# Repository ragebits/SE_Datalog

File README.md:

# SE_Datalog
Diseño de la placa para SE

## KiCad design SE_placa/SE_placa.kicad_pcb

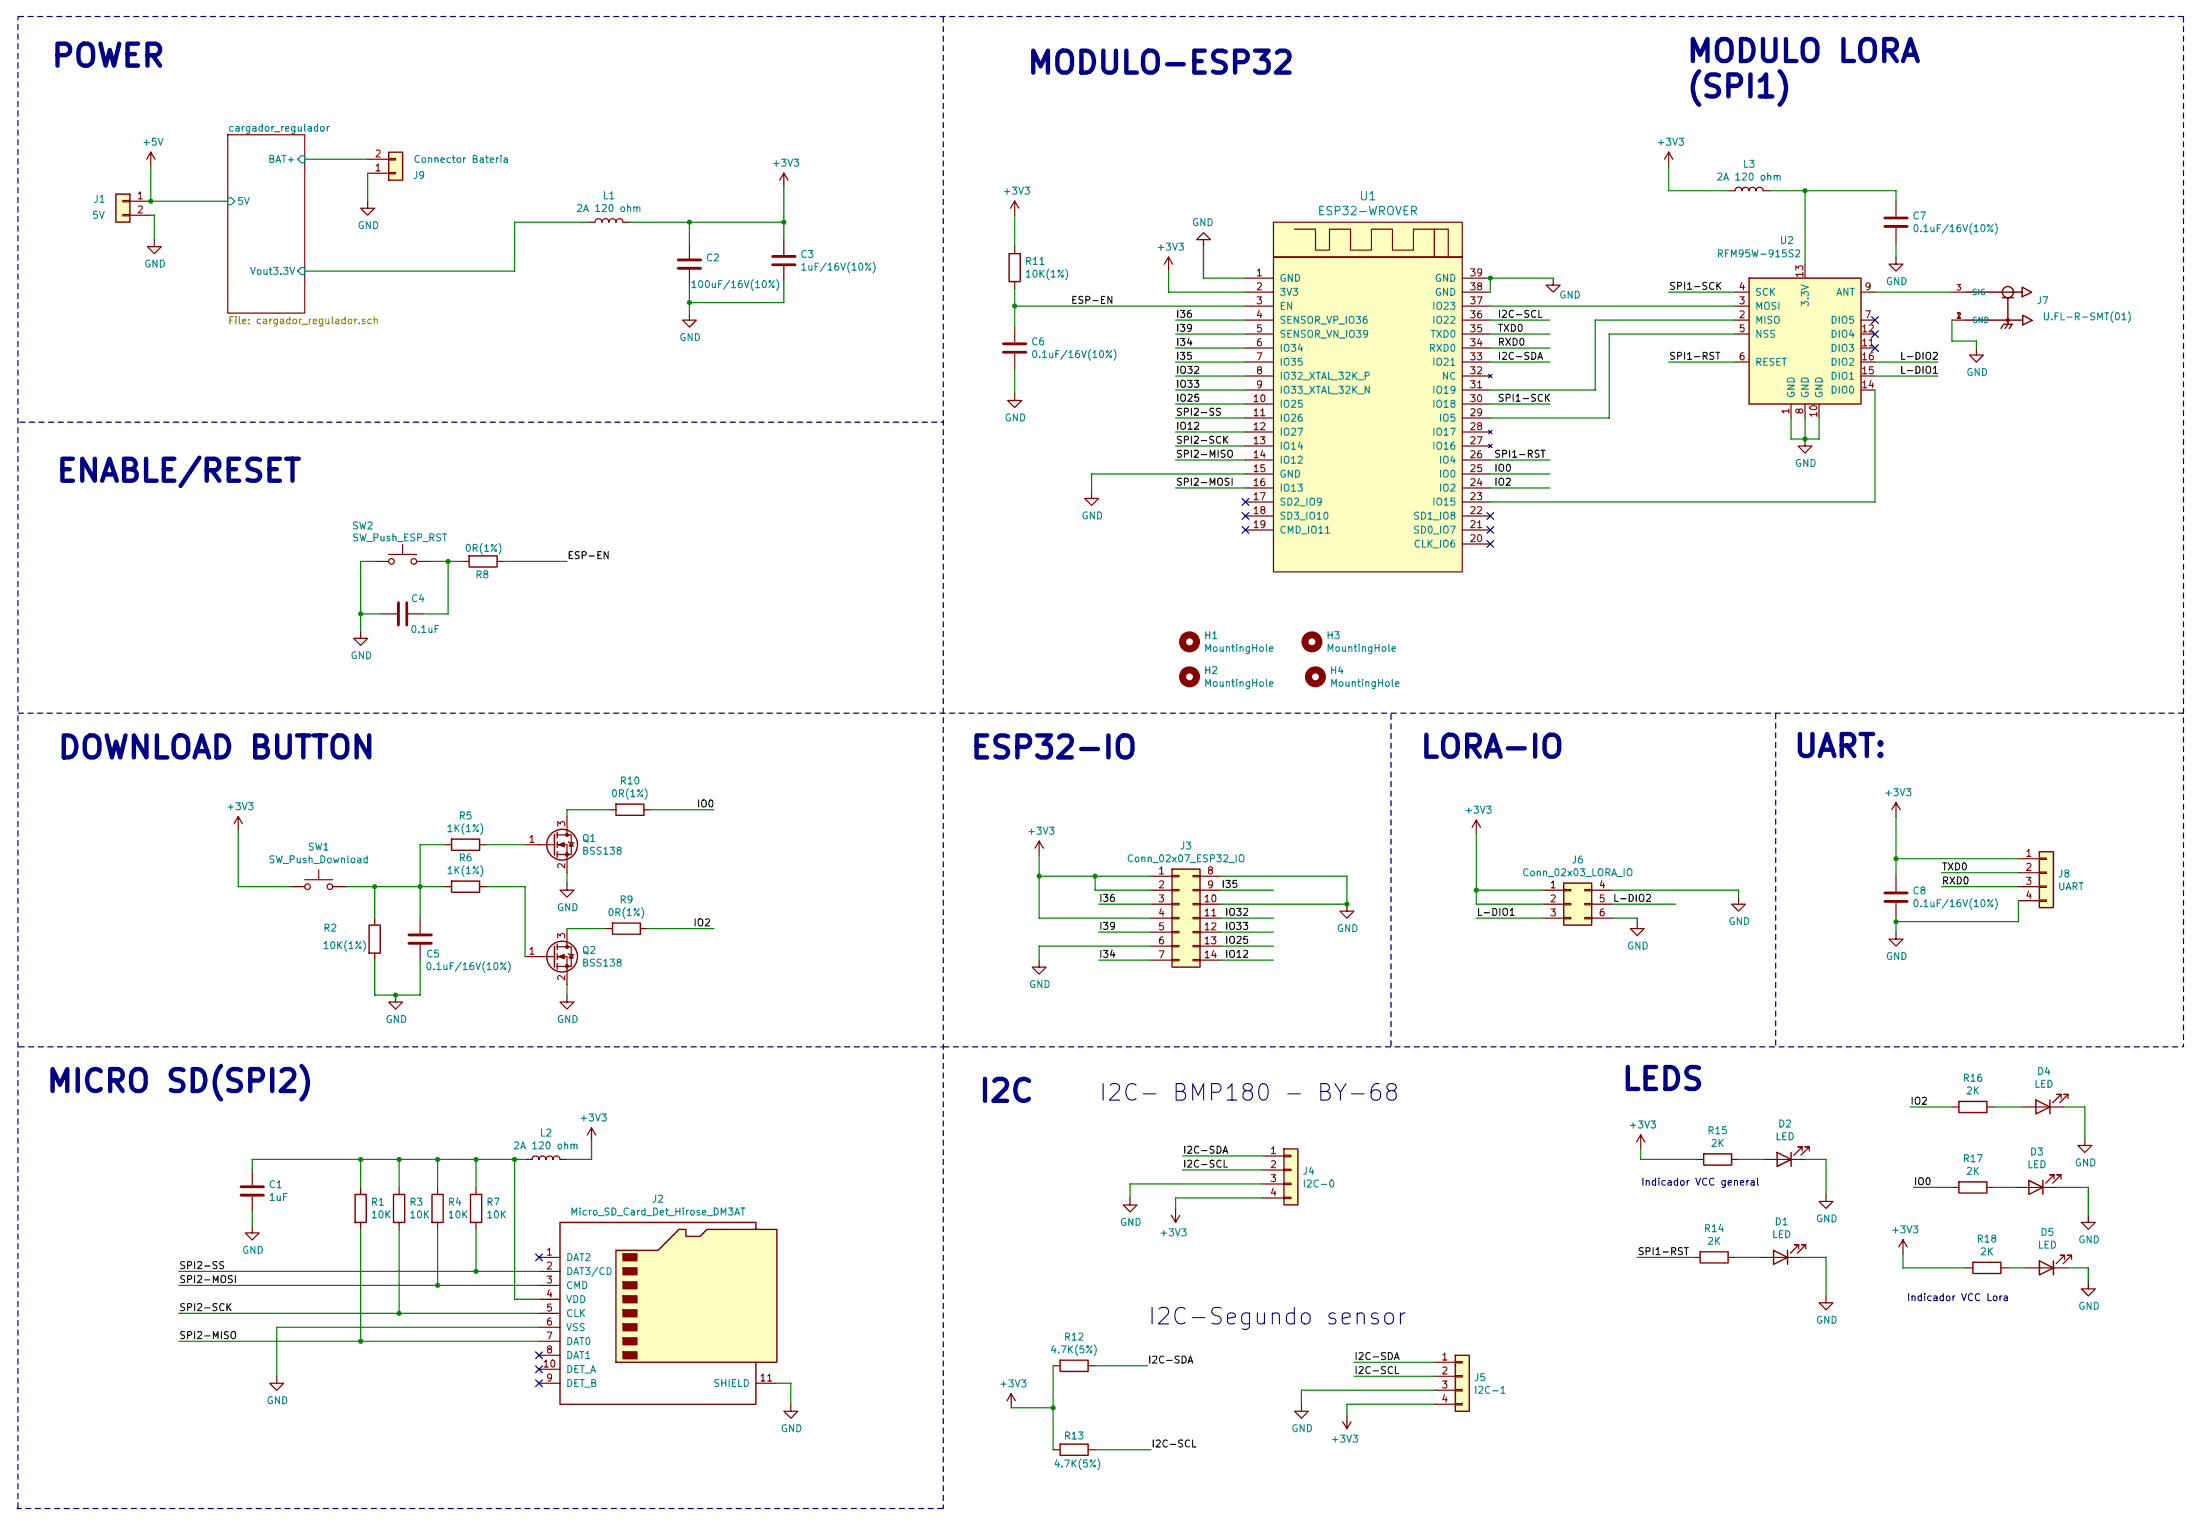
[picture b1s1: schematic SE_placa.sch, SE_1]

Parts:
C1: 1uF; C_0805_2012Metric_Pad1.18x1.45mm_HandSolder
C2: 100uF/16V(10%); C_0805_2012Metric_Pad1.18x1.45mm_HandSolder
C3: 1uF/16V(10%); C_0805_2012Metric_Pad1.18x1.45mm_HandSolder
C4: 0.1uF; C_0805_2012Metric_Pad1.18x1.45mm_HandSolder
C5, C6, C7, C8: 0.1uF/16V(10%); C_0805_2012Metric_Pad1.18x1.45mm_HandSolder
D1, D2, D3, D4, D5: LED; LED_0805_2012Metric_Pad1.15x1.40mm_HandSolder
H1, H2, H3, H4: MountingHole; MountingHole_2.5mm_Pad
J1: 5V; PinHeader_1x02_P2.54mm_Vertical
J2: Micro_SD_Card_Det_Hirose_DM3AT; microSD_HC_Hirose_DM3AT-SF-PEJM5
J3: Conn_02x07_ESP32_IO; PinSocket_2x07_P2.54mm_Vertical
J4: I2C-0; PinSocket_1x04_P2.54mm_Vertical
J5: I2C-1; PinSocket_1x04_P2.54mm_Vertical
J6: Conn_02x03_LORA_IO; PinSocket_2x03_P2.54mm_Vertical
J7: U.FL-R-SMT(01); HRS_U.FL-R-SMT(01)
J8: UART; PinSocket_1x04_P2.54mm_Vertical
J9: Connector Bateria; PinHeader_1x02_P2.54mm_Vertical
L1, L2, L3: 2A 120 ohm; L_0805_2012Metric_Pad1.15x1.40mm_HandSolder
Q1, Q2: BSS138; SOT-23
R1, R3, R4, R7: 10K; R_0805_2012Metric_Pad1.20x1.40mm_HandSolder
R2, R11: 10K(1%); R_0805_2012Metric_Pad1.20x1.40mm_HandSolder
R5, R6: 1K(1%); R_0805_2012Metric_Pad1.20x1.40mm_HandSolder
R8, R9, R10: 0R(1%); R_0805_2012Metric_Pad1.20x1.40mm_HandSolder
R12, R13: 4.7K(5%); R_0805_2012Metric_Pad1.20x1.40mm_HandSolder
R14, R15, R16, R17, R18: 2K; R_0805_2012Metric_Pad1.20x1.40mm_HandSolder
SW1: SW_Push_Download; SW_SPST_CK_RS282G05A3
SW2: SW_Push_ESP_RST; SW_SPST_CK_RS282G05A3
U1: ESP32-WROVER; XCVR_ESP32-WROVER-I
U2: RFM95W-915S2; HOPERF_RFM9XW_SMD

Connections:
+3V3: C2.1, C3.1, C8.1, J3.1, J3.2, J3.4, J4.4, J5.4, J6.1, J6.2, J8.1, L1.2, L2.2, L3.1, R11.2, R12.2, R13.2, R15.2, R18.2, SW1.1, U1.2 (3V3)
+5V: J1.1; also elsewhere on the board
/ESP-EN: C6.2, R8.1, R11.1, U1.3 (EN)
/I2C-SCL: J4.2, J5.2, R13.1, U1.36 (IO22)
/I2C-SDA: J4.1, J5.1, R12.1, U1.33 (IO21)
/I34: J3.7, U1.6 (IO34)
/I35: J3.9, U1.7 (IO35)
/I36: J3.3, U1.4 (SENSOR_VP_IO36)
/I39: J3.5, U1.5 (SENSOR_VN_IO39)
/IO0: R10.1, R17.2, U1.25 (IO0)
/IO2: R9.1, R16.2, U1.24 (IO2)
/IO12: J3.14, U1.12 (IO27)
/IO25: J3.13, U1.10 (IO25)
/IO32: J3.11, U1.8 (IO32_XTAL_32K_P)
/IO33: J3.12, U1.9 (IO33_XTAL_32K_N)
/L-DIO1: J6.3, U2.15 (DIO1)
/L-DIO2: J6.5, U2.16 (DIO2)
/RXD0: J8.3, U1.34 (RXD0)
/SPI1-RST: R14.2, U1.26 (IO4), U2.6 (RESET)
/SPI1-SCK: U1.30 (IO18), U2.4 (SCK)
/SPI2-MISO: J2.7 (DAT0), R1.2, U1.14 (IO12)
/SPI2-MOSI: J2.3 (CMD), R4.2, U1.16 (IO13)
/SPI2-SCK: J2.5 (CLK), R3.2, U1.13 (IO14)
/SPI2-SS: J2.2 (DAT3/CD), R7.2, U1.11 (IO26)
/TXD0: J8.2, U1.35 (TXD0)
/cargador_regulador/BAT+: J9.2; also elsewhere on the board
/cargador_regulador/Vout3.3V: L1.1; also elsewhere on the board
GND: C1.2, C2.2, C3.2, C4.2, C5.2, C6.1, C7.2, C8.2, D1.1 (K), D2.1 (K), D3.1 (K), D4.1 (K), D5.1 (K), J1.2, J2.6 (VSS), J2.11 (SHIELD), J3.6, J3.8, J3.10, J4.3, J5.3, J6.4, J6.6, J7.1 (GND), J7.2 (GND), J8.4, J9.1, Q1.2 (S), Q2.2 (S), R2.2, SW2.1, U1.1 (GND), U1.15 (GND), U1.38 (GND), U1.39 (GND), U2.1 (GND), U2.8 (GND), U2.10 (GND); also elsewhere on the board
unnamed: C1.1, J2.4 (VDD), L2.1, R1.1, R3.1, R4.1, R7.1
unnamed: C4.1, R8.2, SW2.2
unnamed: C5.1, R2.1, R5.2, R6.2, SW1.2
unnamed: C7.1, L3.2, U2.13 (3.3V)
unnamed: D1.2 (A), R14.1
unnamed: D2.2 (A), R15.1
unnamed: D3.2 (A), R17.1
unnamed: D4.2 (A), R16.1
unnamed: D5.2 (A), R18.1
unnamed: J7.3 (SIG), U2.9 (ANT)
unnamed: Q1.1 (G), R5.1
unnamed: Q1.3 (D), R10.2
unnamed: Q2.1 (G), R6.1
unnamed: Q2.3 (D), R9.2
unnamed: U1.23 (IO15), U2.14 (DIO0)
unnamed: U1.29 (IO5), U2.5 (NSS)
unnamed: U1.31 (IO19), U2.2 (MISO)
unnamed: U1.37 (IO23), U2.3 (MOSI)

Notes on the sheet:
POWER
I2C- BMP180 - BY-68
MICRO SD(SPI2)
MODULO-ESP32
MODULO LORA (SPI1)
DOWNLOAD BUTTON
ENABLE/RESET
LEDS
LORA-IO
I2C
I2C-Segundo sensor
ESP32-IO
UART:
Indicador VCC general
Indicador VCC Lora

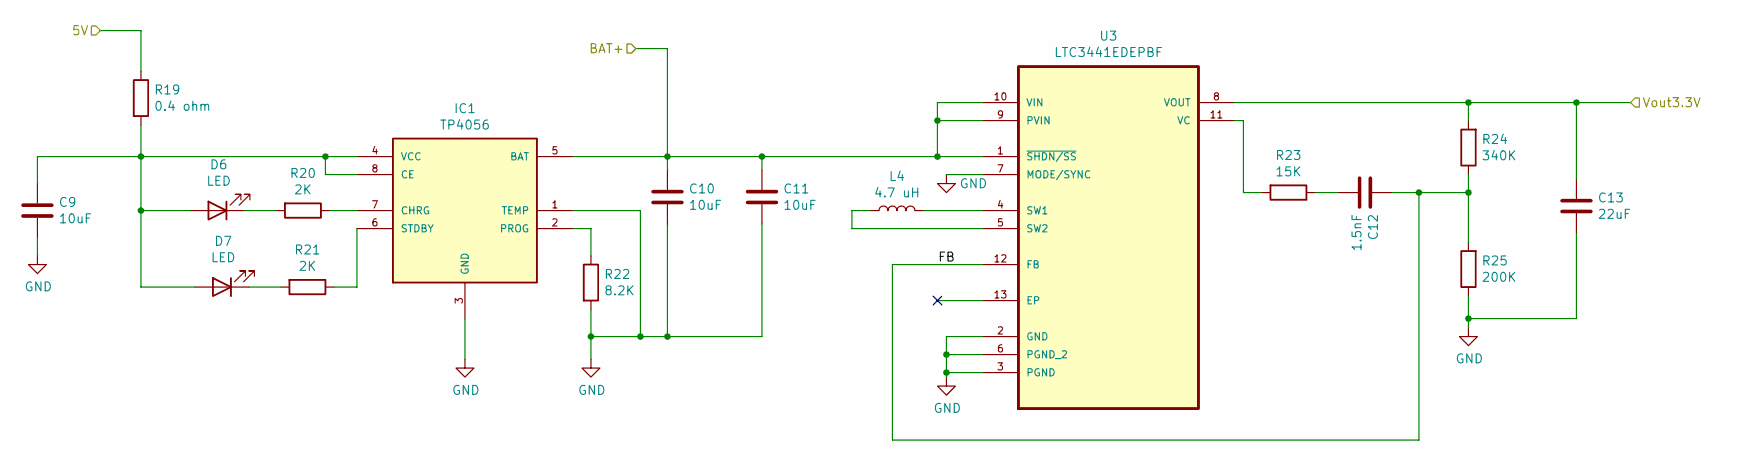
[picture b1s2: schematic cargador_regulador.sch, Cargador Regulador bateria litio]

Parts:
C9, C10, C11: 10uF; C_0805_2012Metric_Pad1.18x1.45mm_HandSolder
C12: 1.5nF; C_0805_2012Metric_Pad1.18x1.45mm_HandSolder
C13: 22uF; C_0805_2012Metric_Pad1.18x1.45mm_HandSolder
D6, D7: LED; LED_0805_2012Metric_Pad1.15x1.40mm_HandSolder
IC1: TP4056; SOP-8
L4: 4.7 uH; IND_1264EY-4R7M=P3
R19: 0.4 ohm; R_0805_2012Metric_Pad1.20x1.40mm_HandSolder
R20, R21: 2K; R_0805_2012Metric_Pad1.20x1.40mm_HandSolder
R22: 8.2K; R_0805_2012Metric_Pad1.20x1.40mm_HandSolder
R23: 15K; R_0805_2012Metric_Pad1.20x1.40mm_HandSolder
R24: 340K; R_0805_2012Metric_Pad1.20x1.40mm_HandSolder
R25: 200K; R_0805_2012Metric_Pad1.20x1.40mm_HandSolder
U3: LTC3441EDEPBF; SON50P300X400X80-13N-D; MPN LTC3441EDE#PBF

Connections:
+5V: R19.1; also elsewhere on the board
/cargador_regulador/BAT+: C10.1, C11.1, IC1.5 (BAT), U3.1 (~SHDN/SS), U3.9 (PVIN), U3.10 (VIN); also elsewhere on the board
/cargador_regulador/FB: C12.1, R24.1, R25.2, U3.12 (FB)
/cargador_regulador/Vout3.3V: C13.1, R24.2, U3.8 (VOUT); also elsewhere on the board
GND: C9.2, C10.2, C11.2, C13.2, IC1.1 (TEMP), IC1.3 (GND), R22.2, R25.1, U3.2 (GND), U3.3 (PGND), U3.6 (PGND_2), U3.7 (MODE/SYNC); also elsewhere on the board
unnamed: C9.1, D6.2 (A), D7.2 (A), IC1.4 (VCC), IC1.8 (CE), R19.2
unnamed: C12.2, R23.1
unnamed: D6.1 (K), R20.2
unnamed: D7.1 (K), R21.2
unnamed: IC1.2 (PROG), R22.1
unnamed: IC1.6 (STDBY), R21.1
unnamed: IC1.7 (CHRG), R20.1
unnamed: L4.1, U3.5 (SW2)
unnamed: L4.2, U3.4 (SW1)
unnamed: R23.2, U3.11 (VC)

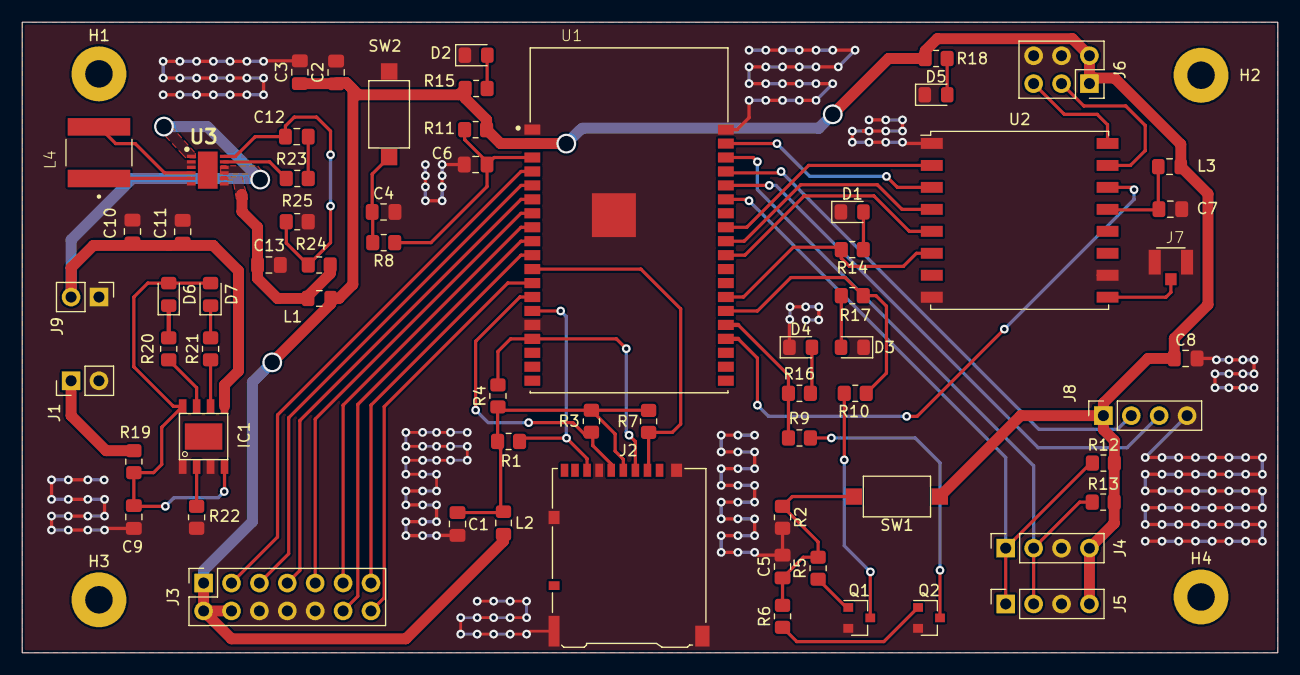
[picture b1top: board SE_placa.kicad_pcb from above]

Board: 2 copper layers, 114.3 x 57.4 mm, 70 parts (0 on the bottom side), 57 nets.

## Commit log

2021-04-13 Creacion de archivos de poyecto
    Creacion de archivos de poyecto
2021-04-15 Agregado de info
    Se agrego información de referencia del diseño y del desarrollo del proyecto . Se incluyo el diagrama de conexionado en kicad
2021-04-15 Carga Listado de distribucion de pin utilizados
    carga Listado de distribucion de pin utilizados y carga de comparativo de seleccion de componentes
2021-04-26 Organizar
    Se organizo la distribución de los espacios, se separo la fuente del ESP32 y la fuente de alimentación
2021-04-26 Cambio modelo de Hoja A3
    organizo hoja de esquematico a formato A3. Incluyo libreria de conector UFL. Organizo Alimentacion, incluyo bobinas para I/O salidas. Incluyo switches de EN y de Programacion IO0, IO2, incluyo alguno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
2021-04-27 Finalizacion del layout
    Se ordeno nuevamente el layout, se completaron conexion de los modulos, se incluyo conexion de I/O del modulo lora al ESP, se incluyeron los I/O de lora. se amplio la cantidad de pines del conector d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
2021-04-28 Se asociaron footprints
    Se pusieron los footprints y se pudo asociar las librerias de los elementos, escogiendolos comercialmente y midiendo con los que ya tengo en mi poder.
2021-04-29 Actualizacion de huellas y correccion de errores de layout
    Corrigieron los errores de layout, se incluyeron power conector y se señalaron los pines que no se concetan, se actualizaron huellas a elementos comerciales, se cambio la huella del Micro SD y del co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
2021-04-29 Actualizacion de PCB solo rutas
    Eliminado un led repetido, el led 5. Primer intento crudo de desarrollar la PCB sin estandares, tamaños de caminos u otras consideraciones tecnicas, solo ruteo para ir entendiendo y aprendiendo cual 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
2021-04-29 reinicio de ruteo
2021-05-04 Corregida Grid, reinciado el PCB
    Crroegido grid a 25 mil, reconectado el layout, se cambiaron ubicación de algunos elementos dentro de la sabana . se retiraron las resistencias de 0 ohm no necesarias en la I/O, se cambio bonina por 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
2021-05-06 Circuito Alimentacion
    Agregado Ic para carga de bateria de litio , agregado IC tipo Buck-bost para asegurar alimentacion 3.3 V 1 A para alimentacion de circuitos. Este circuito esta incluido en una nueva hoja.
2021-05-06 Actualizacion de fechas
2021-05-06 Actualizacion PCB
    Organizo archivos, agrego nuevos elementos a footprint, actualizo net list y actualizo PCB, agrego modelos 3D disponibles. Listo para iniciar ruteo
2021-06-28 Inclusion informacion ref SINK SOURCE
2021-07-01 Organizar integrado rev A
2021-07-06 Ubicaciones de librerias de absolutas a relativas
2021-07-13 ruteo 1
    1. Agregados mounting holes 2.5 mm
    2. Reordeno elementos para hacer mas facil el ruteo.
    3. Ordeno los leds para indicar mejor el estado de lora y alimentacion general
    4. Ordeno lesd y conectores de bateria y alimentacion por panel
    giro conectores de I/o de lora
    en general se dejaron por grupos los elementos de acuerdo al tipo de funcion dentro de la placa
2021-07-13 continuacion de ruteo
    Solo queda por rutear tierras.
    agrego regla de ruteo para el U3 elemento mas pequeño regulador LTC3441, aun siguen generando error la base del elemento.
2021-07-13 ruteo de tierras
2021-07-13 actualizacion tierra
2021-07-15 Ruteo 2
    Aumento el ancho de las pistas de señales a 0.4 m
    aumento las pistas de alimentacion a 1 mm
    modifico ubicacion de elementos para mejorar ruteo evitando pasar por debajo de elementos
2021-07-20 Ruteo 3
    1. Cambio orden de los pines de I/O para hacer mas facil el ruteo de los conectores, modifico ubicacion de I/Os del Lora
    2. Cambio huella del LTC 3441 al parecer la que tenia creaba conflictos con las rutas y sus anchos
    3. cambio el esquema de Net classes a default, arreglando el tamaño de las rutas y de las vias .
    4. Modifico la ruta a 0.3 mm , agrego esto a pre definidas
    5. agrego ruta de 1 mm y vias de 1.8 mm para alimentaciones
    6. cambio ubicaciones de conectorres de bateria y de panel solar
2021-07-20 Ruteo y vias
    Se pusieron zonas para agrandar los caminos falta poner las capas de tierra
2021-07-21 Update SE_placa.kicad_pcb
    Organizando los nombres de los componentes para que se puedan leer
2021-07-21 Gerber files
    Generacion de archivos gerber
2021-07-25 Actualizacion de Modelos 3D
    Actualizo los modelos 3D de todos los elementos, los cargo en el directorio de huellas y modelos del proyecto
